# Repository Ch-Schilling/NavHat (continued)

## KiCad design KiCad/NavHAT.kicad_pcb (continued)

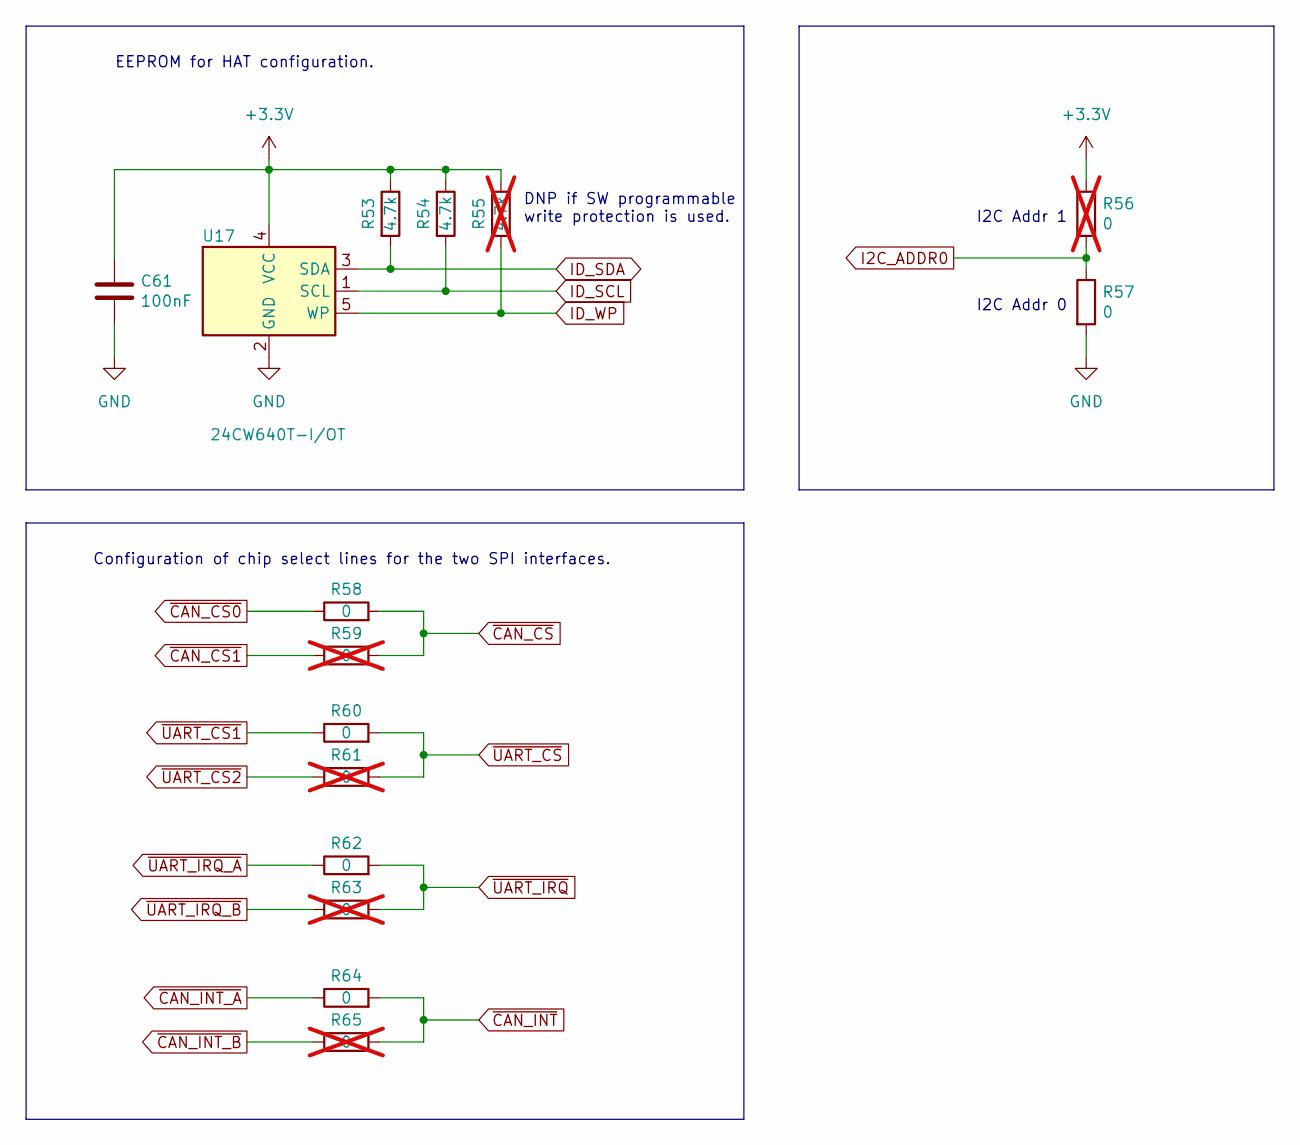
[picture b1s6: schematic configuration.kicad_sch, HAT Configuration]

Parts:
C61: 100nF; C_0402_1005Metric
R53, R54: 4.7k; R_0402_1005Metric
R55: 4.7k; R_0402_1005Metric; not fitted
R56, R59, R61, R63, R65: 0; R_0402_1005Metric; not fitted
R57, R58, R60, R62, R64: 0; R_0402_1005Metric
U17: 24CW640T-I/OT; SOT-23-5

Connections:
+3.3V: C61.1, R53.1, R54.1, R55.1, R56.1, U17.4 (VCC); also elsewhere on the board
GND: C61.2, R57.2, U17.2 (GND); also elsewhere on the board
I2C_ADDR0: R56.2, R57.1; also elsewhere on the board
ID_SCL: R54.2, U17.1 (SCL); also elsewhere on the board
ID_SDA: R53.2, U17.3 (SDA); also elsewhere on the board
ID_WP: R55.2, U17.5 (WP)
~CAN_CS0: R58.1; also elsewhere on the board
~CAN_CS1: R59.1; also elsewhere on the board
~CAN_CS: R58.2, R59.2; also elsewhere on the board
~CAN_INT_A: R64.1; also elsewhere on the board
~CAN_INT_B: R65.1; also elsewhere on the board
~CAN_INT: R64.2, R65.2; also elsewhere on the board
~UART_CS1: R60.1; also elsewhere on the board
~UART_CS2: R61.1; also elsewhere on the board
~UART_CS: R60.2, R61.2; also elsewhere on the board
~UART_IRQ_A: R62.1; also elsewhere on the board
~UART_IRQ_B: R63.1; also elsewhere on the board
~UART_IRQ: R62.2, R63.2; also elsewhere on the board

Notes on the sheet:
DNP if SW programmable write protection is used.
I2C Addr 1
I2C Addr 0
EEPROM for HAT configuration.
Configuration of chip select lines for the two SPI interfaces.

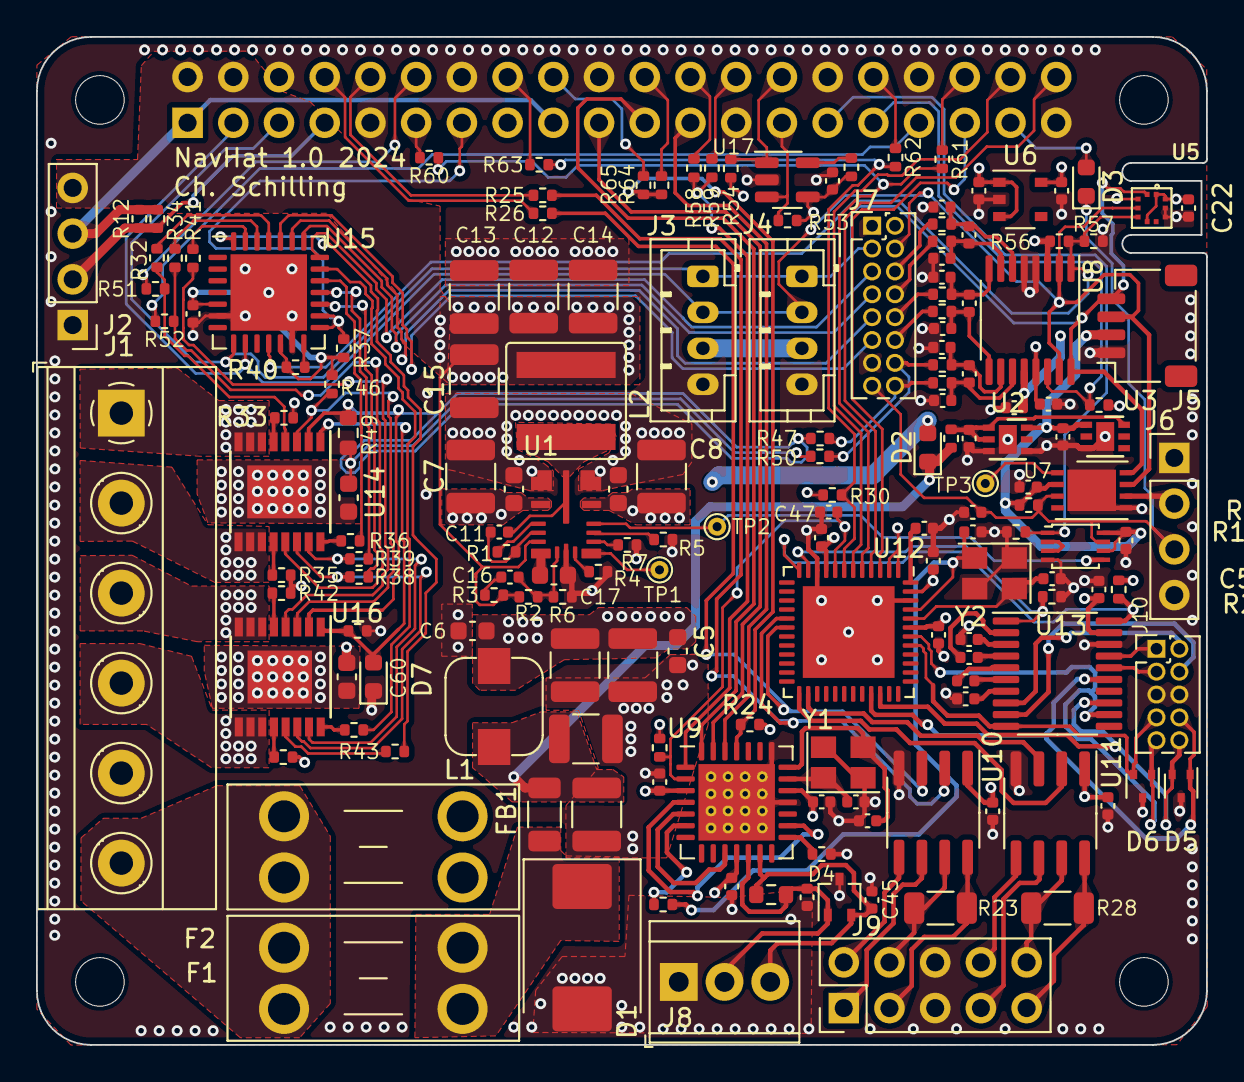
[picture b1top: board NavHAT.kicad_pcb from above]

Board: 4 copper layers, 65.0 x 56.0 mm, 175 parts (1 on the bottom side), 143 nets.

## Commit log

2024-10-04 Create README.md
    First Commit...
2024-11-10 Create NavHAT.md
    Initial setup for documentation.
2024-11-10 KiCad Project
    KiCad Files as the project was ordered the first time.
2024-11-10 PDF of the schematics
2024-11-10 Update with image
2024-11-11 NavHAT.md Power section
2024-11-11 Describing sensor and configuration section.
2024-11-12 Connector descriptions.
2024-11-13 Adding Diagram
2024-11-13 Update NavHAT.md with digram.
2024-11-13 Link to documentation.
2024-11-13 Adding CoC with BOM.
2024-11-17 Create LICENSE
    by chosing cern-ohl-w v2.
2024-11-17 Added license files from cern
2024-11-17 Adding NavHat-Installation.md
    Create separate installation file.
2024-11-17 Add NavHat-Design.md
    Single file for design description.
2024-11-17 Update NavHAT.md
    Outsource Design section, add History
2024-12-04 Added EEPROM configuration documentation.
2024-12-07 adding configuration and scripts for Rasperry eeprom.
2025-01-06 Basic python files to control I2C devices like RTC, ADC, GPIO controller and high side switches. Files are prepared for sphinx documentation.
2025-02-01 Update NavHAT.md
    Including Drivers chapter.
2025-02-01 Create NavHat-Drivers.md
    Adding drivers chapter for CAN and UART.
2025-02-01 Update NavHat-Design.md
    Minor typos and fixes.
